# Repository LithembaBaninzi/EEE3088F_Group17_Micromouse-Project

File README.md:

# EEE3088F_Group17_Micromouse-Project
Designing a micromouse

## Project Overview

Welcome to the Micro-Mouse project for the year 2024! This project involves building subassemblies for your very own simplified micro-mouse, a maze-solving robot. While your micro-mouse may not match the speed of those featured in popular videos, this project serves as an exciting opportunity to delve into hardware design and some minor software components. Let's get started!

### Subsystem Specifications

Detailed specifications and requirements for each subsystem are provided, including pinouts, connector types, power requirements, and considerations for design and functionality.

### Modules Description

#### 1. The Motherboard

- **Description**: The motherboard serves as the base board connecting all other PCBs together.
- **Interface Description**: 
  - Processor board: Two 2x19 (2.54mm pin pitch) pin headers.
  - Motors: Two 2x1 (2.54mm pin pitch) pin headers.
  - Sensor board: 2x14 (2.54mm pin pitch) pin headers.
  - Power board: 2x8 (2.54mm pin pitch) pin headers.

#### 2. The Processor

- **Description**: The processor board features an STM32L476 microcontroller.
- **Interface**: Detailed pinouts are provided for connections.

#### 3. Power Module

- **Description**: Responsible for powering the entire system and charging the battery.
- **Requirements**:
  - Operate 2 motors within specified parameters.
  - Provide analog connection for battery voltage monitoring.
  - Charge the battery from the 5V input pin.
  - Include an ON/OFF switch.

#### 4. Sensor Module

- **Description**: Responsible for detecting/sensing objects in the micro-mouse's path.
- **Requirements**:
  - Detect obstacles in front and possibly on the sides.
  - Design for reliability and power efficiency.
  - Interface with the processor to indicate sensed obstacles.

#### The maze
The maze will have dead ends, multiple paths to the finishing area with each pixel being a 200mm square.
There are multiple paths to get to the goal.
An example is provided below:

## Resources

- [Veritasium Video](https://www.youtube.com/watch?v=JnkMyfQ5YfY) - Watch this video to understand the concept of a micro-mouse.
- Additional resources and documentation are provided within the project repository.

## Conclusion

This README provides an overview of the Micro-Mouse project for 2024, outlining the objectives, module descriptions, and project requirements. Each subsystem has specific tasks and considerations to ensure successful integration into the micro-mouse design. For further details, refer to the project documentation and resources provided. Happy building!
```

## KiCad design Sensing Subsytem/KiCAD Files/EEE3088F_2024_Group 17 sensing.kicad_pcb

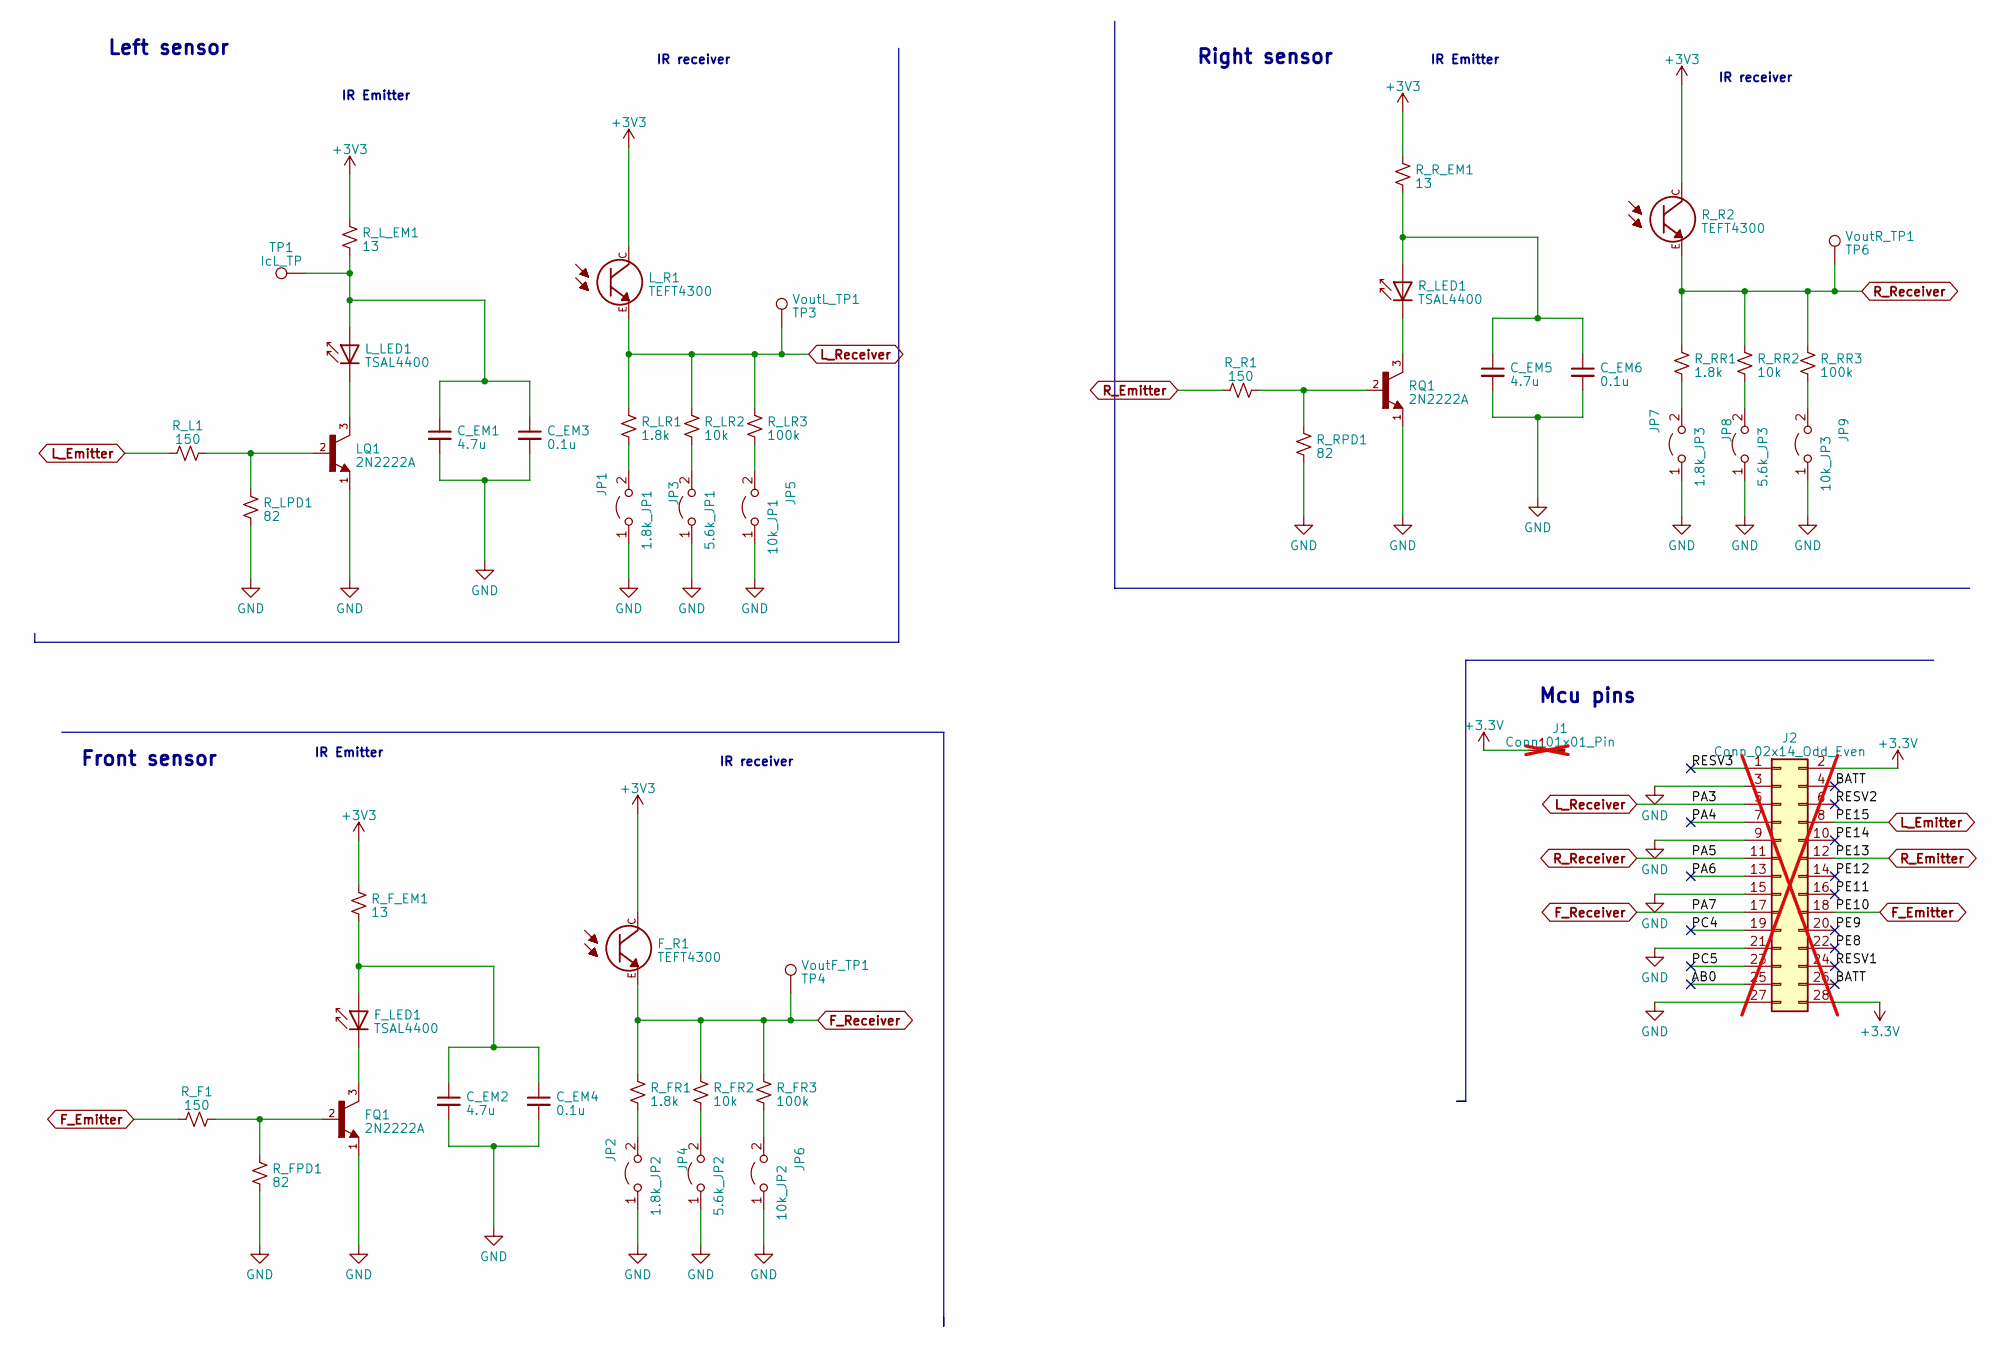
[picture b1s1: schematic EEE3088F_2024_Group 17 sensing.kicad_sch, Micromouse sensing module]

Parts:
1.8k_JP1: JP1; SolderJumper-2_P1.3mm_Open_RoundedPad1.0x1.5mm
1.8k_JP2: JP2; SolderJumper-2_P1.3mm_Open_RoundedPad1.0x1.5mm
1.8k_JP3: JP7; SolderJumper-2_P1.3mm_Open_RoundedPad1.0x1.5mm
5.6k_JP1: JP3; SolderJumper-2_P1.3mm_Open_RoundedPad1.0x1.5mm
5.6k_JP2: JP4; SolderJumper-2_P1.3mm_Open_RoundedPad1.0x1.5mm
5.6k_JP3: JP8; SolderJumper-2_P1.3mm_Open_RoundedPad1.0x1.5mm
10k_JP1: JP5; SolderJumper-2_P1.3mm_Open_RoundedPad1.0x1.5mm
10k_JP2: JP6; SolderJumper-2_P1.3mm_Open_RoundedPad1.0x1.5mm
10k_JP3: JP9; SolderJumper-2_P1.3mm_Open_RoundedPad1.0x1.5mm
C_EM1, C_EM2, C_EM5: 4.7u; C_0201_0603Metric
C_EM3, C_EM4, C_EM6: 0.1u; C_0201_0603Metric
FQ1: 2N2222A; TO92254P470H750-3; PARTREV N/A
F_LED1: TSAL4400; LED_D3.0mm_Horizontal_O1.27mm_Z2.0mm_IRBlack
F_R1: TEFT4300; XDCR_TEFT4300
J1: Conn_01x01_Pin; PinHeader_1x01_P2.54mm_Vertical; not fitted
J2: Conn_02x14_Odd_Even; PinHeader_2x14_P2.54mm_Vertical; not fitted
LQ1: 2N2222A; TO92254P470H750-3; PARTREV N/A
L_LED1: TSAL4400; LED_D3.0mm_Horizontal_O1.27mm_Z2.0mm_IRBlack
L_R1: TEFT4300; XDCR_TEFT4300
RQ1: 2N2222A; TO92254P470H750-3; PARTREV N/A
R_F1: 150; R_0805_2012Metric
R_FPD1: 82; R_0805_2012Metric
R_FR1: 1.8k; R_0805_2012Metric
R_FR2: 10k; R_0805_2012Metric
R_FR3: 100k; R_0805_2012Metric
R_F_EM1: 13; R_0805_2012Metric
R_L1: 150; R_0805_2012Metric
R_LED1: TSAL4400; LED_D3.0mm_Horizontal_O1.27mm_Z2.0mm_IRBlack
R_LPD1: 82; R_0805_2012Metric
R_LR1: 1.8k; R_0805_2012Metric
R_LR2: 10k; R_0805_2012Metric
R_LR3: 100k; R_0805_2012Metric
R_L_EM1: 13; R_0805_2012Metric
R_R1: 150; R_0805_2012Metric
R_R2: TEFT4300; XDCR_TEFT4300
R_RPD1: 82; R_0805_2012Metric
R_RR1: 1.8k; R_0805_2012Metric
R_RR2: 10k; R_0805_2012Metric
R_RR3: 100k; R_0805_2012Metric
R_R_EM1: 13; R_0805_2012Metric
TP1: IcL_TP; TestPoint_Pad_D2.0mm
VoutF_TP1: TP4; TestPoint_Pad_D2.0mm
VoutL_TP1: TP3; TestPoint_Pad_D2.0mm
VoutR_TP1: TP6; TestPoint_Pad_D2.0mm

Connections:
+3.3V: J1.1, J2.2, J2.28
+3V3: F_R1.C, L_R1.C, R_F_EM1.1, R_L_EM1.1, R_R2.C, R_R_EM1.1
/AB0: J2.25
/BATT: J2.4, J2.26
/PA4: J2.7
/PA6: J2.13
/PC4: J2.19
/PC5: J2.23
/PE8: J2.22
/PE9: J2.20
/PE11: J2.16
/PE12: J2.14
/PE14: J2.10
/RESV1: J2.24
/RESV2: J2.6
/RESV3: J2.1
F_Emitter: J2.18, R_F1.1
F_Receiver: F_R1.E, J2.17, R_FR1.1, R_FR2.1, R_FR3.1, VoutF_TP1.1
GND: 1.8k_JP1.1 (A), 1.8k_JP2.1 (A), 1.8k_JP3.1 (A), 5.6k_JP1.1 (A), 5.6k_JP2.1 (A), 5.6k_JP3.1 (A), 10k_JP1.1 (A), 10k_JP2.1 (A), 10k_JP3.1 (A), C_EM1.2, C_EM2.2, C_EM3.2, C_EM4.2, C_EM5.2, C_EM6.2, FQ1.1, J2.3, J2.9, J2.15, J2.21, J2.27, LQ1.1, RQ1.1, R_FPD1.2, R_LPD1.2, R_RPD1.2
L_Emitter: J2.8, R_L1.1
L_Receiver: J2.5, L_R1.E, R_LR1.1, R_LR2.1, R_LR3.1, VoutL_TP1.1
unnamed: 1.8k_JP1.2 (B), R_LR1.2
unnamed: 1.8k_JP2.2 (B), R_FR1.2
unnamed: 1.8k_JP3.2 (B), R_RR1.2
unnamed: 5.6k_JP1.2 (B), R_LR2.2
unnamed: 5.6k_JP2.2 (B), R_FR2.2
unnamed: 5.6k_JP3.2 (B), R_RR2.2
unnamed: 10k_JP1.2 (B), R_LR3.2
unnamed: 10k_JP2.2 (B), R_FR3.2
unnamed: 10k_JP3.2 (B), R_RR3.2
unnamed: FQ1.2, R_F1.2, R_FPD1.1
unnamed: C_EM2.1, C_EM4.1, F_LED1.2 (A), R_F_EM1.2
unnamed: FQ1.3, F_LED1.1 (K)
unnamed: LQ1.2, R_L1.2, R_LPD1.1
unnamed: C_EM1.1, C_EM3.1, L_LED1.2 (A), R_L_EM1.2, TP1.1
unnamed: LQ1.3, L_LED1.1 (K)
unnamed: RQ1.2, R_R1.2, R_RPD1.1
unnamed: C_EM5.1, C_EM6.1, R_LED1.2 (A), R_R_EM1.2
unnamed: RQ1.3, R_LED1.1 (K)
R_Emitter: J2.12, R_R1.1
R_Receiver: J2.11, R_R2.E, R_RR1.1, R_RR2.1, R_RR3.1, VoutR_TP1.1

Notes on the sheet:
IR Emitter
IR receiver
Right sensor
Left sensor
Mcu pins
Front sensor

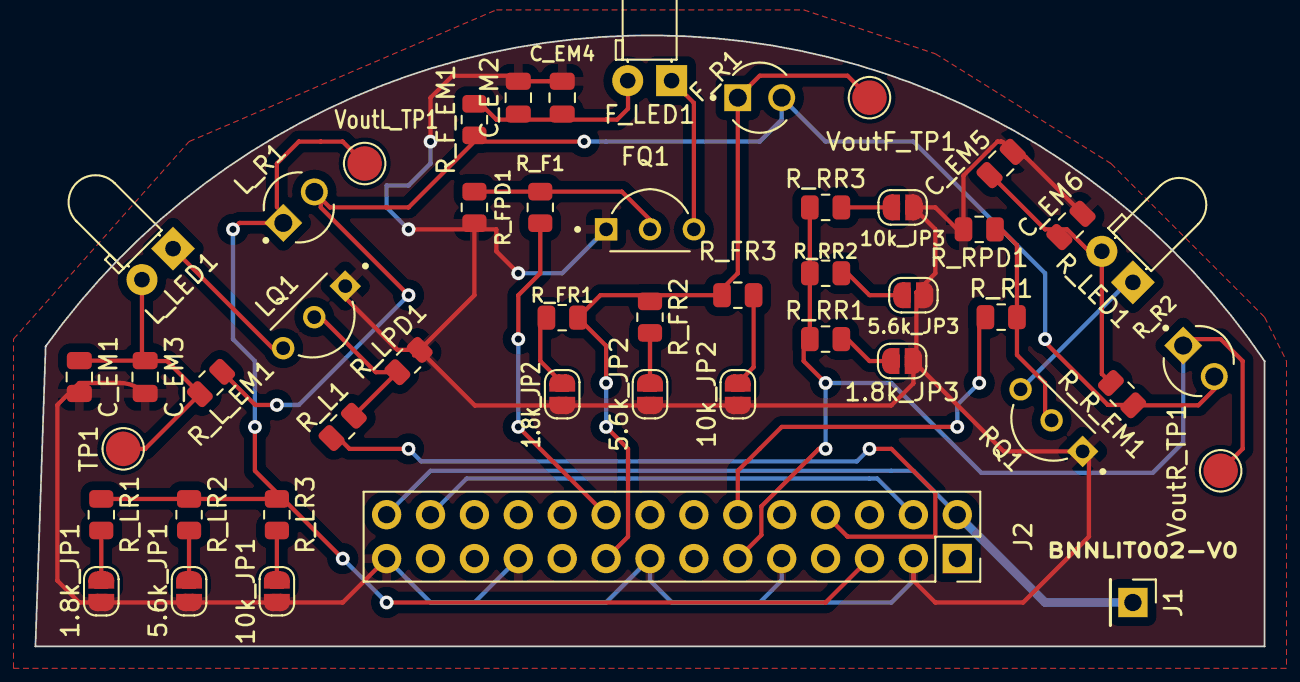
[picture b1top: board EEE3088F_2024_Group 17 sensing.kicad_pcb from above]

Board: 2 copper layers, 71.1 x 35.4 mm, 48 parts (0 on the bottom side), 28 nets.

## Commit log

2024-03-30 Update README.md
    updating the readme file for this project
2024-04-04 Update README.md
    adding pictures
2024-04-04 Create Power Subsystem
2024-04-04 Adding gerber files, CPL file and BOM
2024-04-21 Uploading KiCad Files
2024-05-17 Adding STM32 Cube IDE
    Zip file containing all the code used for the sensing module
